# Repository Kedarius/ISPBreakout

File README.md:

# ISPBreakout
ATmega328PB ICSP/UART breakout

## Description
ATmega328PB has a second UART port that is sharing pins with ICSP/SPI. While this can be handy for debugging you may need to swap ICSP and UART dongles. This breakout board features:
* ICSP in connector, UART in connector
* ICSP out connector
* switches that enables/disables the shared pins in ICSP and UART ports
* switch to choose if the device should be powered from ICSP or UART
* reset button for the ATmega328PB
* (Optional) Power LED

## Assembly

This PCB is designed to be beginner friendly. All you need to populate are the through hole switches and 2.54mm headers. The button and SMD LED (0805) are optional - a great way to start with SMD components.

### Parts
* 3x DPDT On-On 2.54mm pitch switch - i.e. https://lcsc.com/product-detail/Toggle-Switches_Korean-Hroparts-Elec-K3-2235D-F1_C189615.html
* 1x 2x3 2.54 female pin header (angled)
* 1x 2x3 2.54 male pin header (angled)
* 1x 1x4 2.54 male pin header (angled)
* (optional) 1x 6mm tactile switch - i.e. https://lcsc.com/product-detail/Tactile-Switches_ALPSALPINE-SKHHBYA010_C139760.html
* (optional) 1x 0805 SMD LED 
* (optional) 1x 0805 10K SMD resistor

## Demo

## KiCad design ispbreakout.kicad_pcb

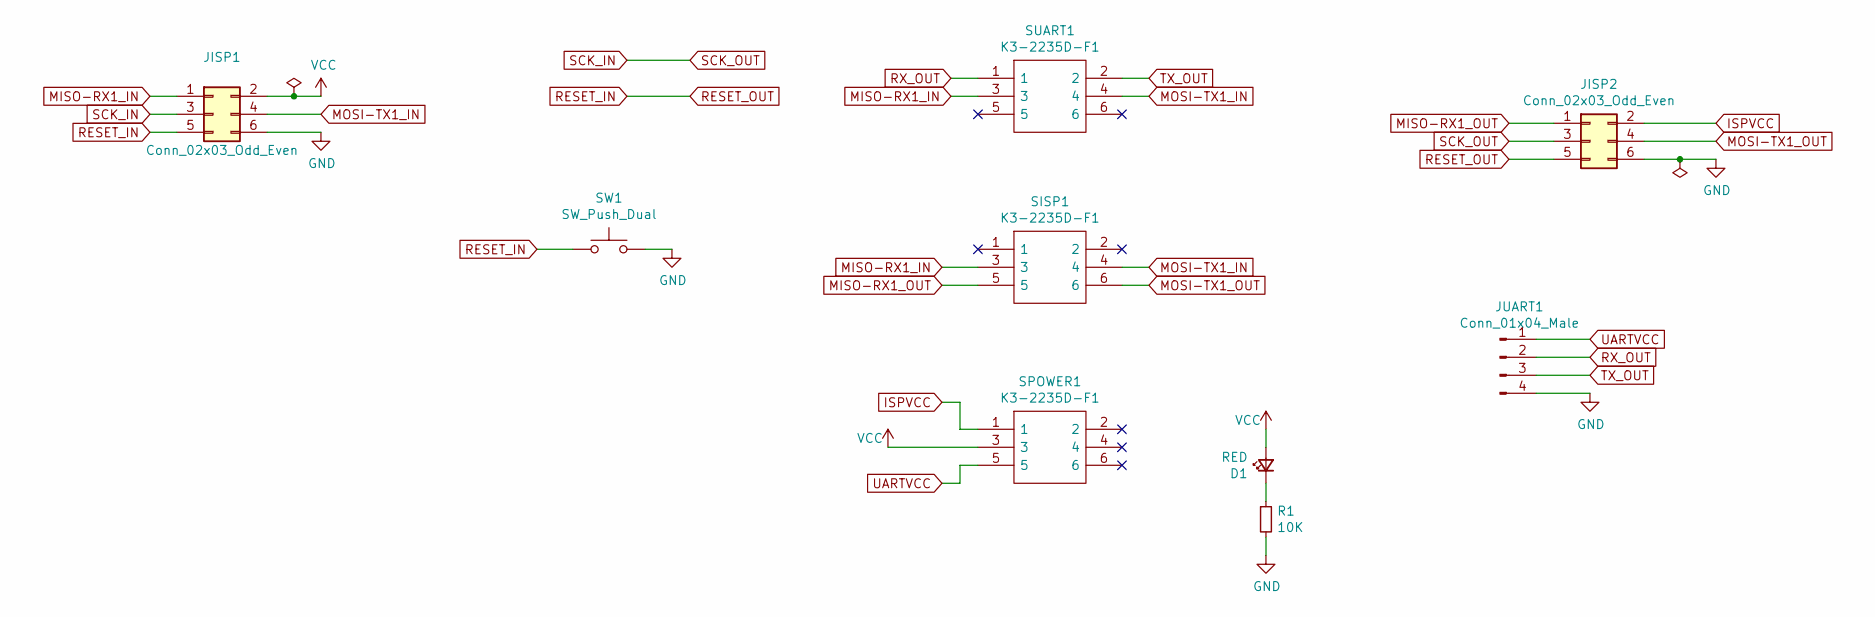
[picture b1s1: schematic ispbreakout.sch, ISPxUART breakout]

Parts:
D1: RED; LED_0805_2012Metric_Pad1.15x1.40mm_HandSolder
JISP1: Conn_02x03_Odd_Even; PinSocket_2x03_P2.54mm_Horizontal
JISP2: Conn_02x03_Odd_Even; PinHeader_2x03_P2.54mm_Horizontal
JUART1: Conn_01x04_Male; PinHeader_1x04_P2.54mm_Horizontal
R1: 10K; R_0805_2012Metric_Pad1.15x1.40mm_HandSolder
SISP1: K3-2235D-F1; K32235DF1; Manufacturer_Part_Number K3-2235D-F1
SPOWER1: K3-2235D-F1; K32235DF1; Manufacturer_Part_Number K3-2235D-F1
SUART1: K3-2235D-F1; K32235DF1; Manufacturer_Part_Number K3-2235D-F1
SW1: SW_Push_Dual; SW_PUSH_6mm

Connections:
GND: JISP1.6, JISP2.6, JUART1.4, R1.2, SW1.2
ISPVCC: JISP2.2, SPOWER1.1
MISO-RX1_IN: JISP1.1, SISP1.3, SUART1.3
MISO-RX1_OUT: JISP2.1, SISP1.5
MOSI-TX1_IN: JISP1.4, SISP1.4, SUART1.4
MOSI-TX1_OUT: JISP2.4, SISP1.6
unnamed: D1.1 (K), R1.1
RESET_IN: JISP1.5, JISP2.5, SW1.1
RX_OUT: JUART1.2, SUART1.1
SCK_IN: JISP1.3, JISP2.3
TX_OUT: JUART1.3, SUART1.2
UARTVCC: JUART1.1, SPOWER1.5
VCC: D1.2 (A), JISP1.2, SPOWER1.3

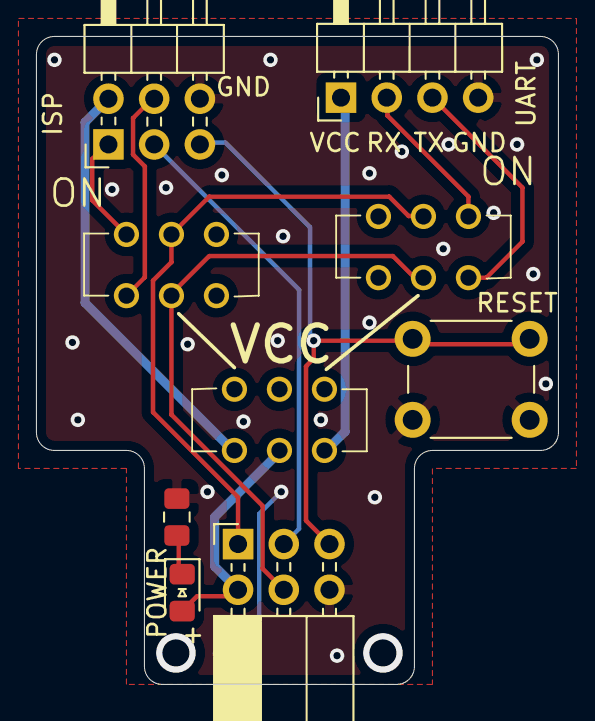
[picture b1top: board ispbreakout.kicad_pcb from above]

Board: 2 copper layers, 29.0 x 36.0 mm, 9 parts (0 on the bottom side), 13 nets.

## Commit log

2021-03-07 ver1
2021-03-08 * Add images
